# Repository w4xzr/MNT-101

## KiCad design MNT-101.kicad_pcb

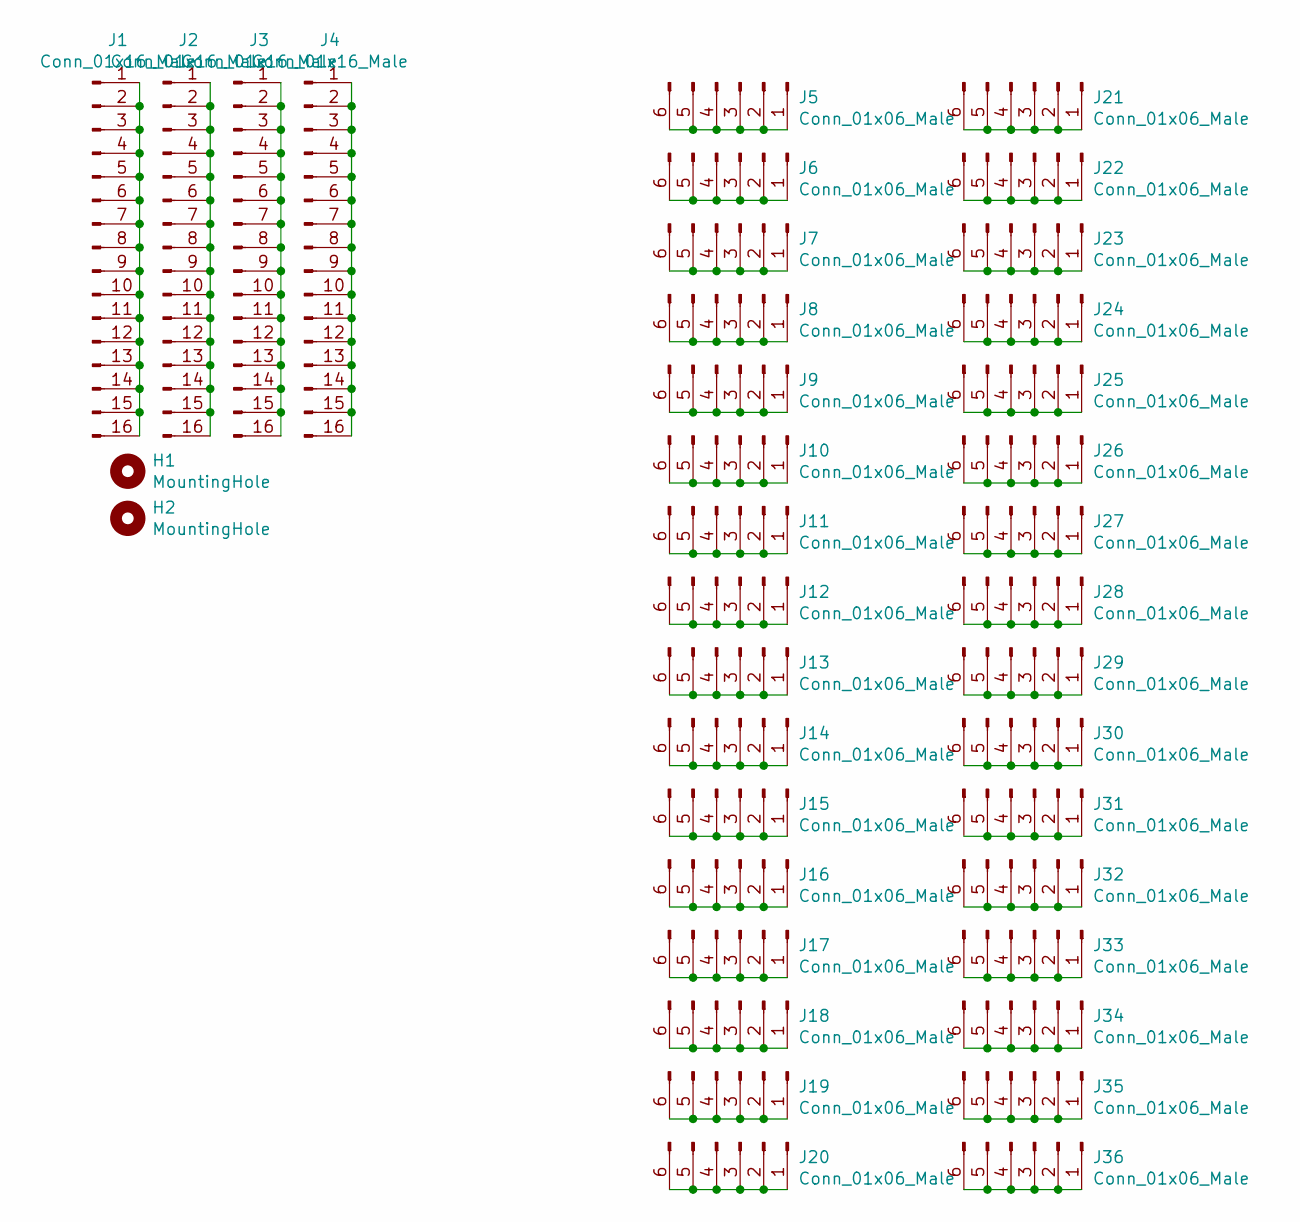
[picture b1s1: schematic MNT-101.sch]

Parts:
H1, H2: MountingHole; MountingHole_2.7mm_M2.5
J1, J2, J3, J4: Conn_01x16_Male; PinHeader_1x16_P2.54mm_Vertical
J5, J6, J7, J8, J9, J10, J11, J12, J13, J14, J15, J16, J17, J18, J19, J20, J21, J22, J23, J24, J25, J26, J27, J28, J29, J30, J31, J32, J33, J34, J35, J36: Conn_01x06_Male; PinHeader_1x06_P2.54mm_Vertical

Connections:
unnamed: J1.1, J1.2, J1.3, J1.4, J1.5, J1.6, J1.7, J1.8, J1.9, J1.10, J1.11, J1.12, J1.13, J1.14, J1.15, J1.16
unnamed: J2.1, J2.2, J2.3, J2.4, J2.5, J2.6, J2.7, J2.8, J2.9, J2.10, J2.11, J2.12, J2.13, J2.14, J2.15, J2.16
unnamed: J3.1, J3.2, J3.3, J3.4, J3.5, J3.6, J3.7, J3.8, J3.9, J3.10, J3.11, J3.12, J3.13, J3.14, J3.15, J3.16
unnamed: J4.1, J4.2, J4.3, J4.4, J4.5, J4.6, J4.7, J4.8, J4.9, J4.10, J4.11, J4.12, J4.13, J4.14, J4.15, J4.16
unnamed: J5.1, J5.2, J5.3, J5.4, J5.5, J5.6
unnamed: J6.1, J6.2, J6.3, J6.4, J6.5, J6.6
unnamed: J7.1, J7.2, J7.3, J7.4, J7.5, J7.6
unnamed: J8.1, J8.2, J8.3, J8.4, J8.5, J8.6
unnamed: J9.1, J9.2, J9.3, J9.4, J9.5, J9.6
unnamed: J10.1, J10.2, J10.3, J10.4, J10.5, J10.6
unnamed: J11.1, J11.2, J11.3, J11.4, J11.5, J11.6
unnamed: J12.1, J12.2, J12.3, J12.4, J12.5, J12.6
unnamed: J13.1, J13.2, J13.3, J13.4, J13.5, J13.6
unnamed: J14.1, J14.2, J14.3, J14.4, J14.5, J14.6
unnamed: J15.1, J15.2, J15.3, J15.4, J15.5, J15.6
unnamed: J16.1, J16.2, J16.3, J16.4, J16.5, J16.6
unnamed: J17.1, J17.2, J17.3, J17.4, J17.5, J17.6
unnamed: J18.1, J18.2, J18.3, J18.4, J18.5, J18.6
unnamed: J19.1, J19.2, J19.3, J19.4, J19.5, J19.6
unnamed: J20.1, J20.2, J20.3, J20.4, J20.5, J20.6
unnamed: J21.1, J21.2, J21.3, J21.4, J21.5, J21.6
unnamed: J22.1, J22.2, J22.3, J22.4, J22.5, J22.6
unnamed: J23.1, J23.2, J23.3, J23.4, J23.5, J23.6
unnamed: J24.1, J24.2, J24.3, J24.4, J24.5, J24.6
unnamed: J25.1, J25.2, J25.3, J25.4, J25.5, J25.6
unnamed: J26.1, J26.2, J26.3, J26.4, J26.5, J26.6
unnamed: J27.1, J27.2, J27.3, J27.4, J27.5, J27.6
unnamed: J28.1, J28.2, J28.3, J28.4, J28.5, J28.6
unnamed: J29.1, J29.2, J29.3, J29.4, J29.5, J29.6
unnamed: J30.1, J30.2, J30.3, J30.4, J30.5, J30.6
unnamed: J31.1, J31.2, J31.3, J31.4, J31.5, J31.6
unnamed: J32.1, J32.2, J32.3, J32.4, J32.5, J32.6
unnamed: J33.1, J33.2, J33.3, J33.4, J33.5, J33.6
unnamed: J34.1, J34.2, J34.3, J34.4, J34.5, J34.6
unnamed: J35.1, J35.2, J35.3, J35.4, J35.5, J35.6
unnamed: J36.1, J36.2, J36.3, J36.4, J36.5, J36.6

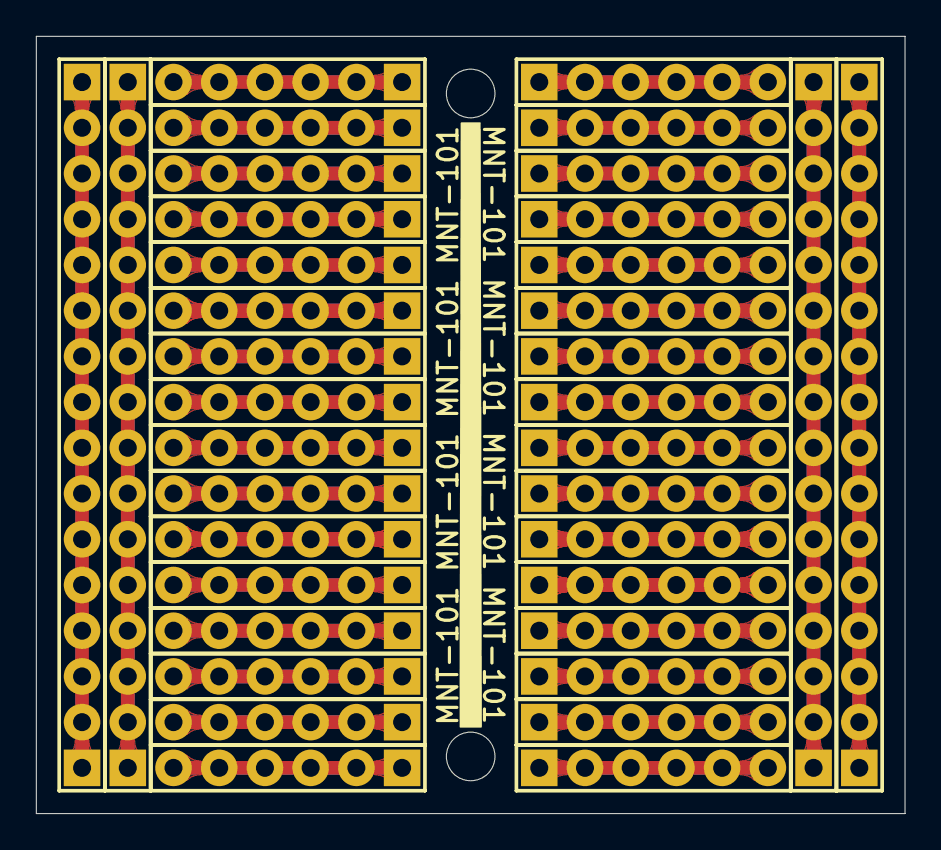
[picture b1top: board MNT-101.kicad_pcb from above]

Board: 2 copper layers, 48.3 x 43.2 mm, 38 parts (0 on the bottom side), 36 nets.

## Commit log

2020-07-03 init
2020-07-03 Updated Images: Fri Jul 3 23:37:42 UTC 2020 (Build 2)
    [skip ci]
2020-07-03 [ImgBot] Optimize images
    *Total -- 2,047.02kb -> 1,390.89kb (32.05%)
    /Images/Back.png -- 1,037.96kb -> 692.00kb (33.33%)
    /Images/Front.png -- 1,009.05kb -> 698.88kb (30.74%)
2020-07-03 Added README.md
2020-07-04 Updated Images: Sat Jul 4 00:02:14 UTC 2020 (Build 7)
    [skip ci]
2020-07-04 Cleanup
2020-07-04 Updated Images: Sat Jul 4 00:33:20 UTC 2020 (Build 12)
    [skip ci]
2020-07-04 Updated Images: Sat Jul 4 01:47:40 UTC 2020 (Build 18)
    [skip ci]
2020-07-04 Updated Images: Sat Jul 4 02:12:18 UTC 2020 (Build 23)
    [skip ci]
